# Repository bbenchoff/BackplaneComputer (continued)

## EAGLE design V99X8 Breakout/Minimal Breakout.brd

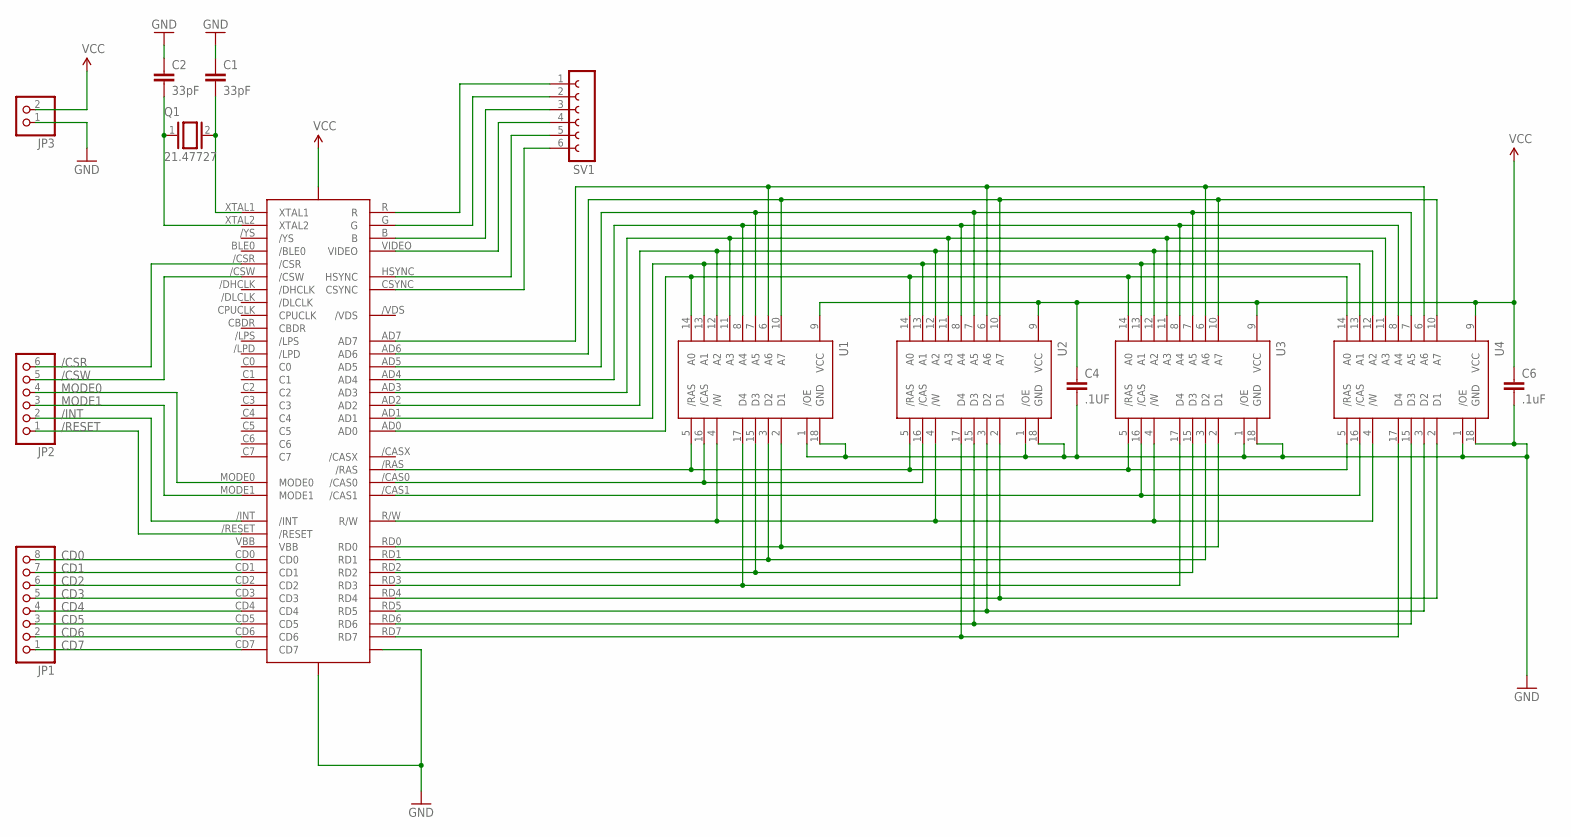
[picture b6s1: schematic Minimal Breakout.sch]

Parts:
C1, C2: 33pF; CAP-PTH-SMALLEZ
C4: .1UF; CAP-PTH-SMALLEZ
C6: .1uF; CAP-PTH-SMALLEZ
JP1: PINHD-1X8; 1X08
JP2: PINHD-1X6; 1X06
JP3: PINHD-1X2; 1X02
Q1: 21.47727; Q
SV1: FE06-1; FE06
U1, U2, U3, U4: 41464; DIL18
V99X8: V99X8

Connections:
/CAS0: U1.16 (/CAS), U2.16 (/CAS), V99X8./CAS0
/CAS1: U3.16 (/CAS), U4.16 (/CAS), V99X8./CAS1
/CSR: JP2.6, V99X8./CSR
/CSW: JP2.5, V99X8./CSW
/INT: JP2.2, V99X8./INT
/RAS: U1.5 (/RAS), U2.5 (/RAS), U3.5 (/RAS), U4.5 (/RAS), V99X8./RAS
/RESET: JP2.1, V99X8./RESET
AD0: U1.14 (A0), U2.14 (A0), U3.14 (A0), U4.14 (A0), V99X8.AD0
AD1: U1.13 (A1), U2.13 (A1), U3.13 (A1), U4.13 (A1), V99X8.AD1
AD2: U1.12 (A2), U2.12 (A2), U3.12 (A2), U4.12 (A2), V99X8.AD2
AD3: U1.11 (A3), U2.11 (A3), U3.11 (A3), U4.11 (A3), V99X8.AD3
AD4: U1.8 (A4), U2.8 (A4), U3.8 (A4), U4.8 (A4), V99X8.AD4
AD5: U1.7 (A5), U2.7 (A5), U3.7 (A5), U4.7 (A5), V99X8.AD5
AD6: U1.10 (A7), U2.10 (A7), U3.10 (A7), U4.10 (A7), V99X8.AD6
AD7: U1.6 (A6), U2.6 (A6), U3.6 (A6), U4.6 (A6), V99X8.AD7
B: SV1.3, V99X8.B
CD0: JP1.8, V99X8.CD0
CD1: JP1.7, V99X8.CD1
CD2: JP1.6, V99X8.CD2
CD3: JP1.5, V99X8.CD3
CD4: JP1.4, V99X8.CD4
CD5: JP1.3, V99X8.CD5
CD6: JP1.2, V99X8.CD6
CD7: JP1.1, V99X8.CD7
CSYNC: SV1.6, V99X8.CSYNC
G: SV1.2, V99X8.G
GND: C1.1, C2.1, C4.2, C6.2, JP3.1, U1.1 (/OE), U1.18 (GND), U2.1 (/OE), U2.18 (GND), U3.1 (/OE), U3.18 (GND), U4.1 (/OE), U4.18 (GND), V99X8.GND, V99X8.GND/DAC (GNDDAC)
HSYNC: SV1.5, V99X8.HSYNC
MODE0: JP2.4, V99X8.MODE0
MODE1: JP2.3, V99X8.MODE1
unnamed: C1.2, Q1.2, V99X8.XTAL1
unnamed: C2.2, Q1.1, V99X8.XTAL2
R: SV1.1, V99X8.R
R/W: U1.4 (/W), U2.4 (/W), U3.4 (/W), U4.4 (/W), V99X8.R/W
RD0: U1.2 (D1), U3.2 (D1), V99X8.RD0
RD1: U1.3 (D2), U3.3 (D2), V99X8.RD1
RD2: U1.15 (D3), U3.15 (D3), V99X8.RD2
RD3: U1.17 (D4), U3.17 (D4), V99X8.RD3
RD4: U2.2 (D1), U4.2 (D1), V99X8.RD4
RD5: U2.3 (D2), U4.3 (D2), V99X8.RD5
RD6: U2.15 (D3), U4.15 (D3), V99X8.RD6
RD7: U2.17 (D4), U4.17 (D4), V99X8.RD7
VBB: V99X8.VBB
VCC: C4.1, C6.1, JP3.2, U1.9 (VCC), U2.9 (VCC), U3.9 (VCC), U4.9 (VCC), V99X8.VCC
VIDEO: SV1.4, V99X8.VIDEO

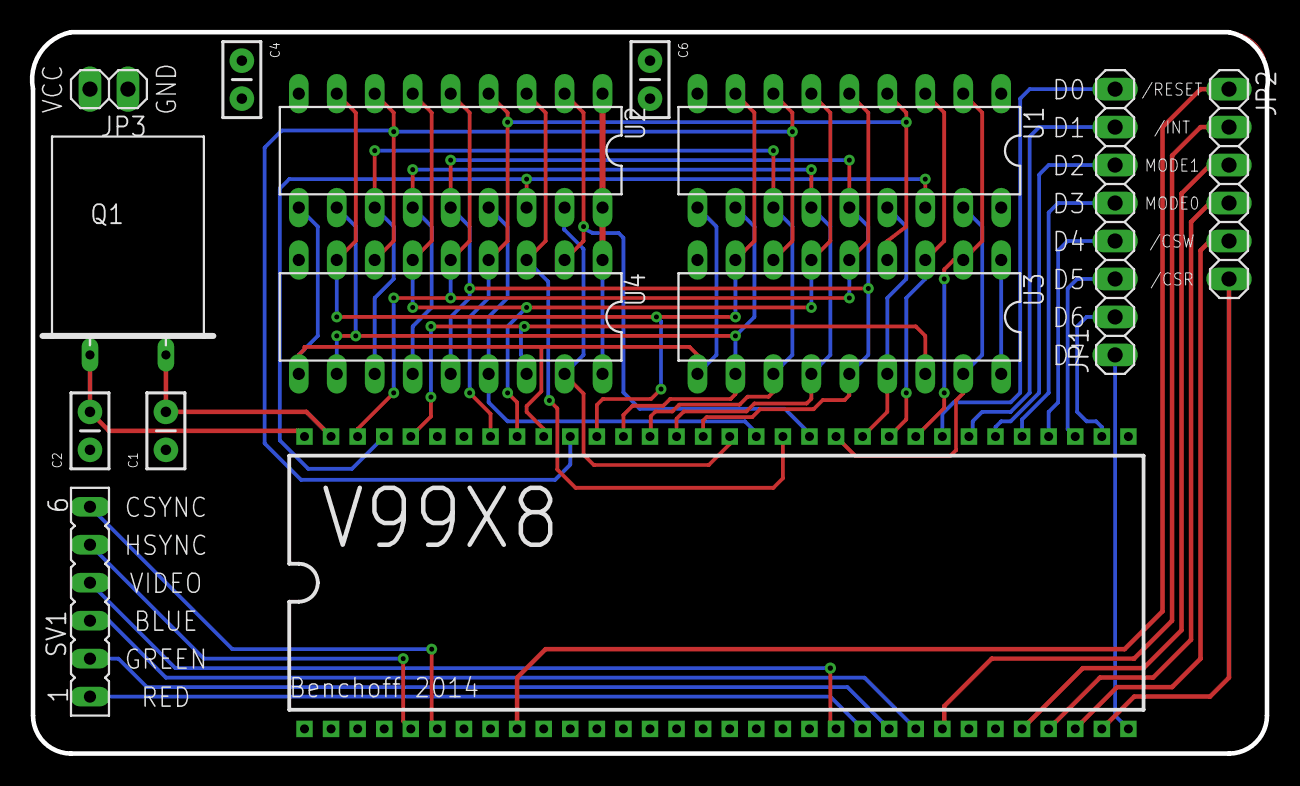
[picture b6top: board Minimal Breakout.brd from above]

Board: 2 copper layers, 82.7 x 48.3 mm, 14 parts (0 on the bottom side), 44 nets.

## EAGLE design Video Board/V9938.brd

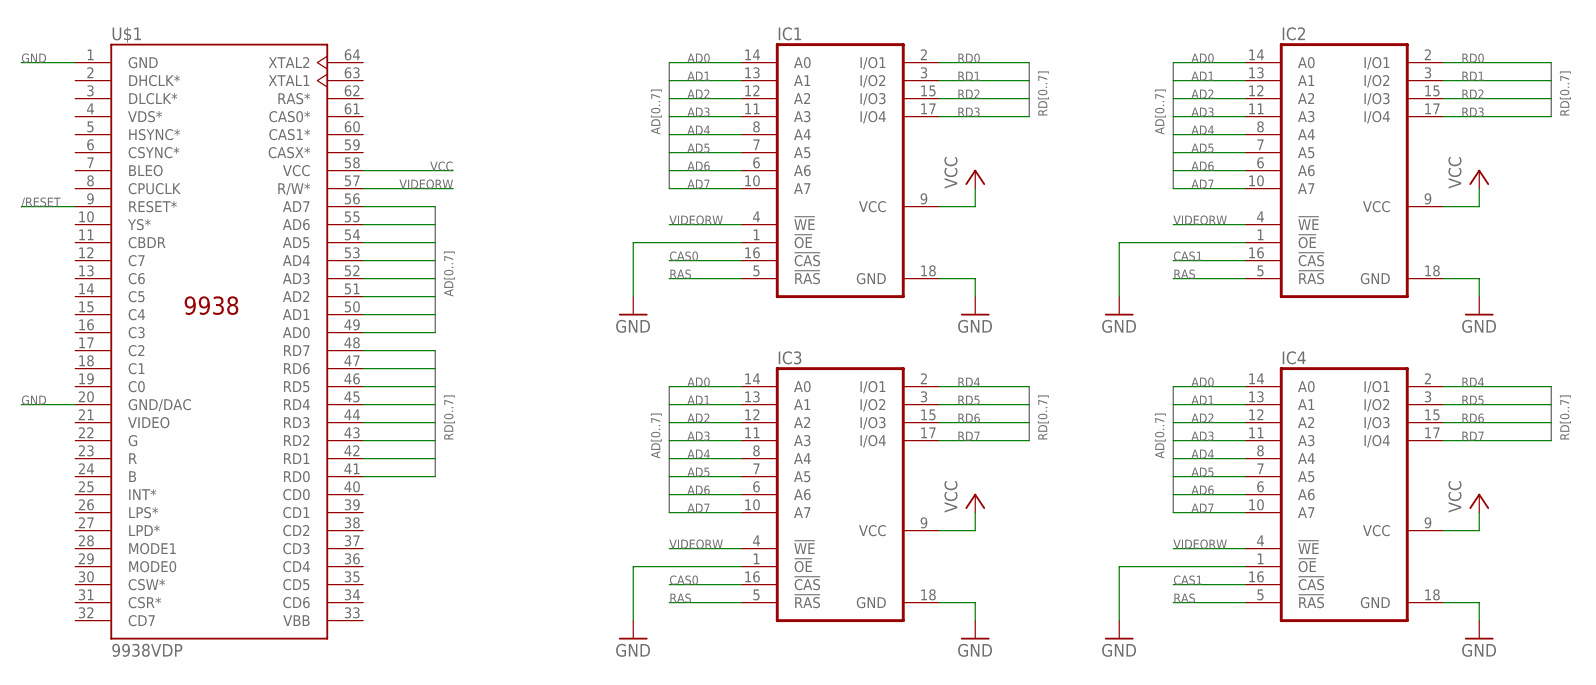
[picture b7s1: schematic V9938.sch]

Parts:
IC1, IC2, IC3, IC4: 41464C; DIL18
U$1: 9938VDP; DIL64-600

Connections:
/RESET: U$1.9 (RESET*)
AD0: IC1.14 (A0), IC2.14 (A0), IC3.14 (A0), IC4.14 (A0), U$1.49 (AD0)
AD1: IC1.13 (A1), IC2.13 (A1), IC3.13 (A1), IC4.13 (A1), U$1.50 (AD1)
AD2: IC1.12 (A2), IC2.12 (A2), IC3.12 (A2), IC4.12 (A2), U$1.51 (AD2)
AD3: IC1.11 (A3), IC2.11 (A3), IC3.11 (A3), IC4.11 (A3), U$1.52 (AD3)
AD4: IC1.8 (A4), IC2.8 (A4), IC3.8 (A4), IC4.8 (A4), U$1.53 (AD4)
AD5: IC1.7 (A5), IC2.7 (A5), IC3.7 (A5), IC4.7 (A5), U$1.54 (AD5)
AD6: IC1.6 (A6), IC2.6 (A6), IC3.6 (A6), IC4.6 (A6), U$1.55 (AD6)
AD7: IC1.10 (A7), IC2.10 (A7), IC3.10 (A7), IC4.10 (A7), U$1.56 (AD7)
CAS0: IC1.16 (!CAS), IC3.16 (!CAS)
CAS1: IC2.16 (!CAS), IC4.16 (!CAS)
GND: IC1.1 (!OE), IC1.18 (GND), IC2.1 (!OE), IC2.18 (GND), IC3.1 (!OE), IC3.18 (GND), IC4.1 (!OE), IC4.18 (GND), U$1.1 (GND), U$1.20 (GND/DAC)
RAS: IC1.5 (!RAS), IC2.5 (!RAS), IC3.5 (!RAS), IC4.5 (!RAS)
RD0: IC1.2 (I/O1), IC2.2 (I/O1), U$1.41 (RD0)
RD1: IC1.3 (I/O2), IC2.3 (I/O2), U$1.42 (RD1)
RD2: IC1.15 (I/O3), IC2.15 (I/O3), U$1.43 (RD2)
RD3: IC1.17 (I/O4), IC2.17 (I/O4), U$1.44 (RD3)
RD4: IC3.2 (I/O1), IC4.2 (I/O1), U$1.45 (RD4)
RD5: IC3.3 (I/O2), IC4.3 (I/O2), U$1.46 (RD5)
RD6: IC3.15 (I/O3), IC4.15 (I/O3), U$1.47 (RD6)
RD7: IC3.17 (I/O4), IC4.17 (I/O4), U$1.48 (RD7)
VCC: IC1.9 (VCC), IC2.9 (VCC), IC3.9 (VCC), IC4.9 (VCC), U$1.58 (VCC)
VIDEORW: IC1.4 (!WE), IC2.4 (!WE), IC3.4 (!WE), IC4.4 (!WE), U$1.57 (R/W*)

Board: 2 copper layers, 5 parts (0 on the bottom side), 22 nets, no tracks yet.

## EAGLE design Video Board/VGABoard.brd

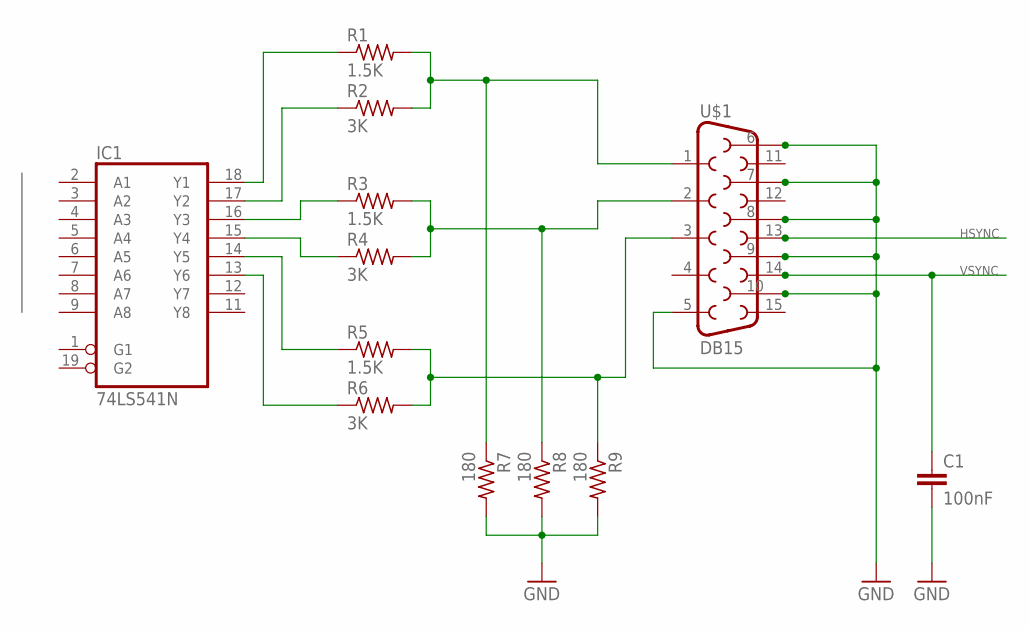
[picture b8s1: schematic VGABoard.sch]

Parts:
C1: 100nF; CAP-PTH-SMALLEZ
IC1: 74LS541N; DIL20
R1, R3, R5: 1.5K; 0204/5
R2, R4, R6: 3K; 0204/5
R7, R8, R9: 180; 0204/5
U$1: DB15

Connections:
GND: C1.2, IC1.10 (GND), R7.2, R8.2, R9.2, U$1.5, U$1.6, U$1.7, U$1.8, U$1.9, U$1.10
HSYNC: U$1.13
unnamed: IC1.18 (Y1), R1.1
unnamed: IC1.17 (Y2), R2.1
unnamed: IC1.16 (Y3), R3.1
unnamed: IC1.15 (Y4), R4.1
unnamed: IC1.13 (Y6), R6.1
unnamed: IC1.14 (Y5), R5.1
unnamed: R1.2, R2.2, R7.1, U$1.1
unnamed: R3.2, R4.2, R8.1, U$1.2
unnamed: R5.2, R6.2, R9.1, U$1.3
VCC: IC1.20 (VCC)
VSYNC: C1.1, U$1.14

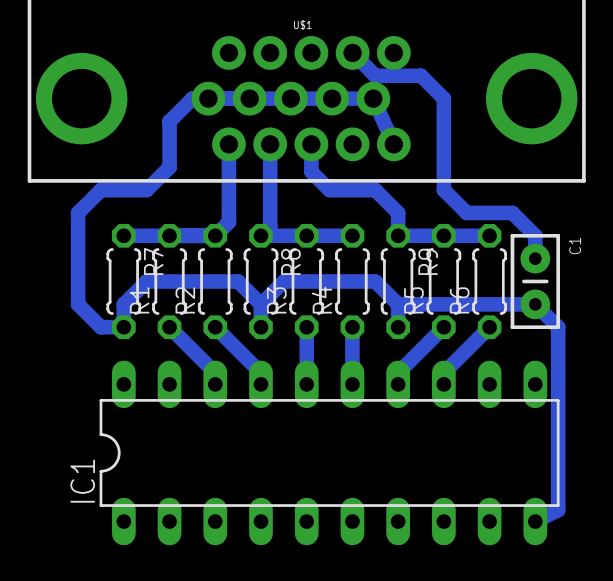
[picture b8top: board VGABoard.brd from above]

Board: 2 copper layers, 12 parts (0 on the bottom side), 11 nets.

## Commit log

2013-12-15 Create
2013-12-15 Added Eagle files and Gerbers
2013-12-15 Added BOM
2013-12-15 Got rid of crap
2013-12-15 Added BOM, Gerbers
2013-12-16 Added blank wirewrap board and clock module
2013-12-17 Fixed fit between backplane & enclosure
2013-12-17 Updated blank board gerbers
2013-12-17 Added enclosure cutouts
2013-12-20 Fixed issue with drill file in backplane gerbers
2013-12-21 Fixed enclosure cutouts, added SIMM board
2013-12-25 Fixed a whole lot of shit
2014-01-13 Fixed more crap
2014-02-19 Added chip labels
2014-03-24 Added V99X8 breakout and front panel
2014-03-24 fixed front panel
2014-03-24 made standoffs higher
2014-03-24 Added .IGS file
2014-03-25 Frontplane THAT MIGHT WORK THIS TIME
2014-03-25 Moved everything 0.03 inches
2015-01-11 Fixed scale of front panel
2015-01-21 Fixed the mini front plane
    It didn't work before, so there ya go
2015-01-21 Something?
2015-01-22 Started Big Frontplane template
2015-02-13 Updated Front Panel
2015-02-13 deleted unneeded
2015-02-14 Enclosure Update
    Changed panel screw mounts to 6-32, changed height, exported to .stl and
    .iges
2015-03-03 Built breakout board and RAM card
2015-03-24 Milled Front Panel
    Added files from the SeeMeCNC front panel expedition
